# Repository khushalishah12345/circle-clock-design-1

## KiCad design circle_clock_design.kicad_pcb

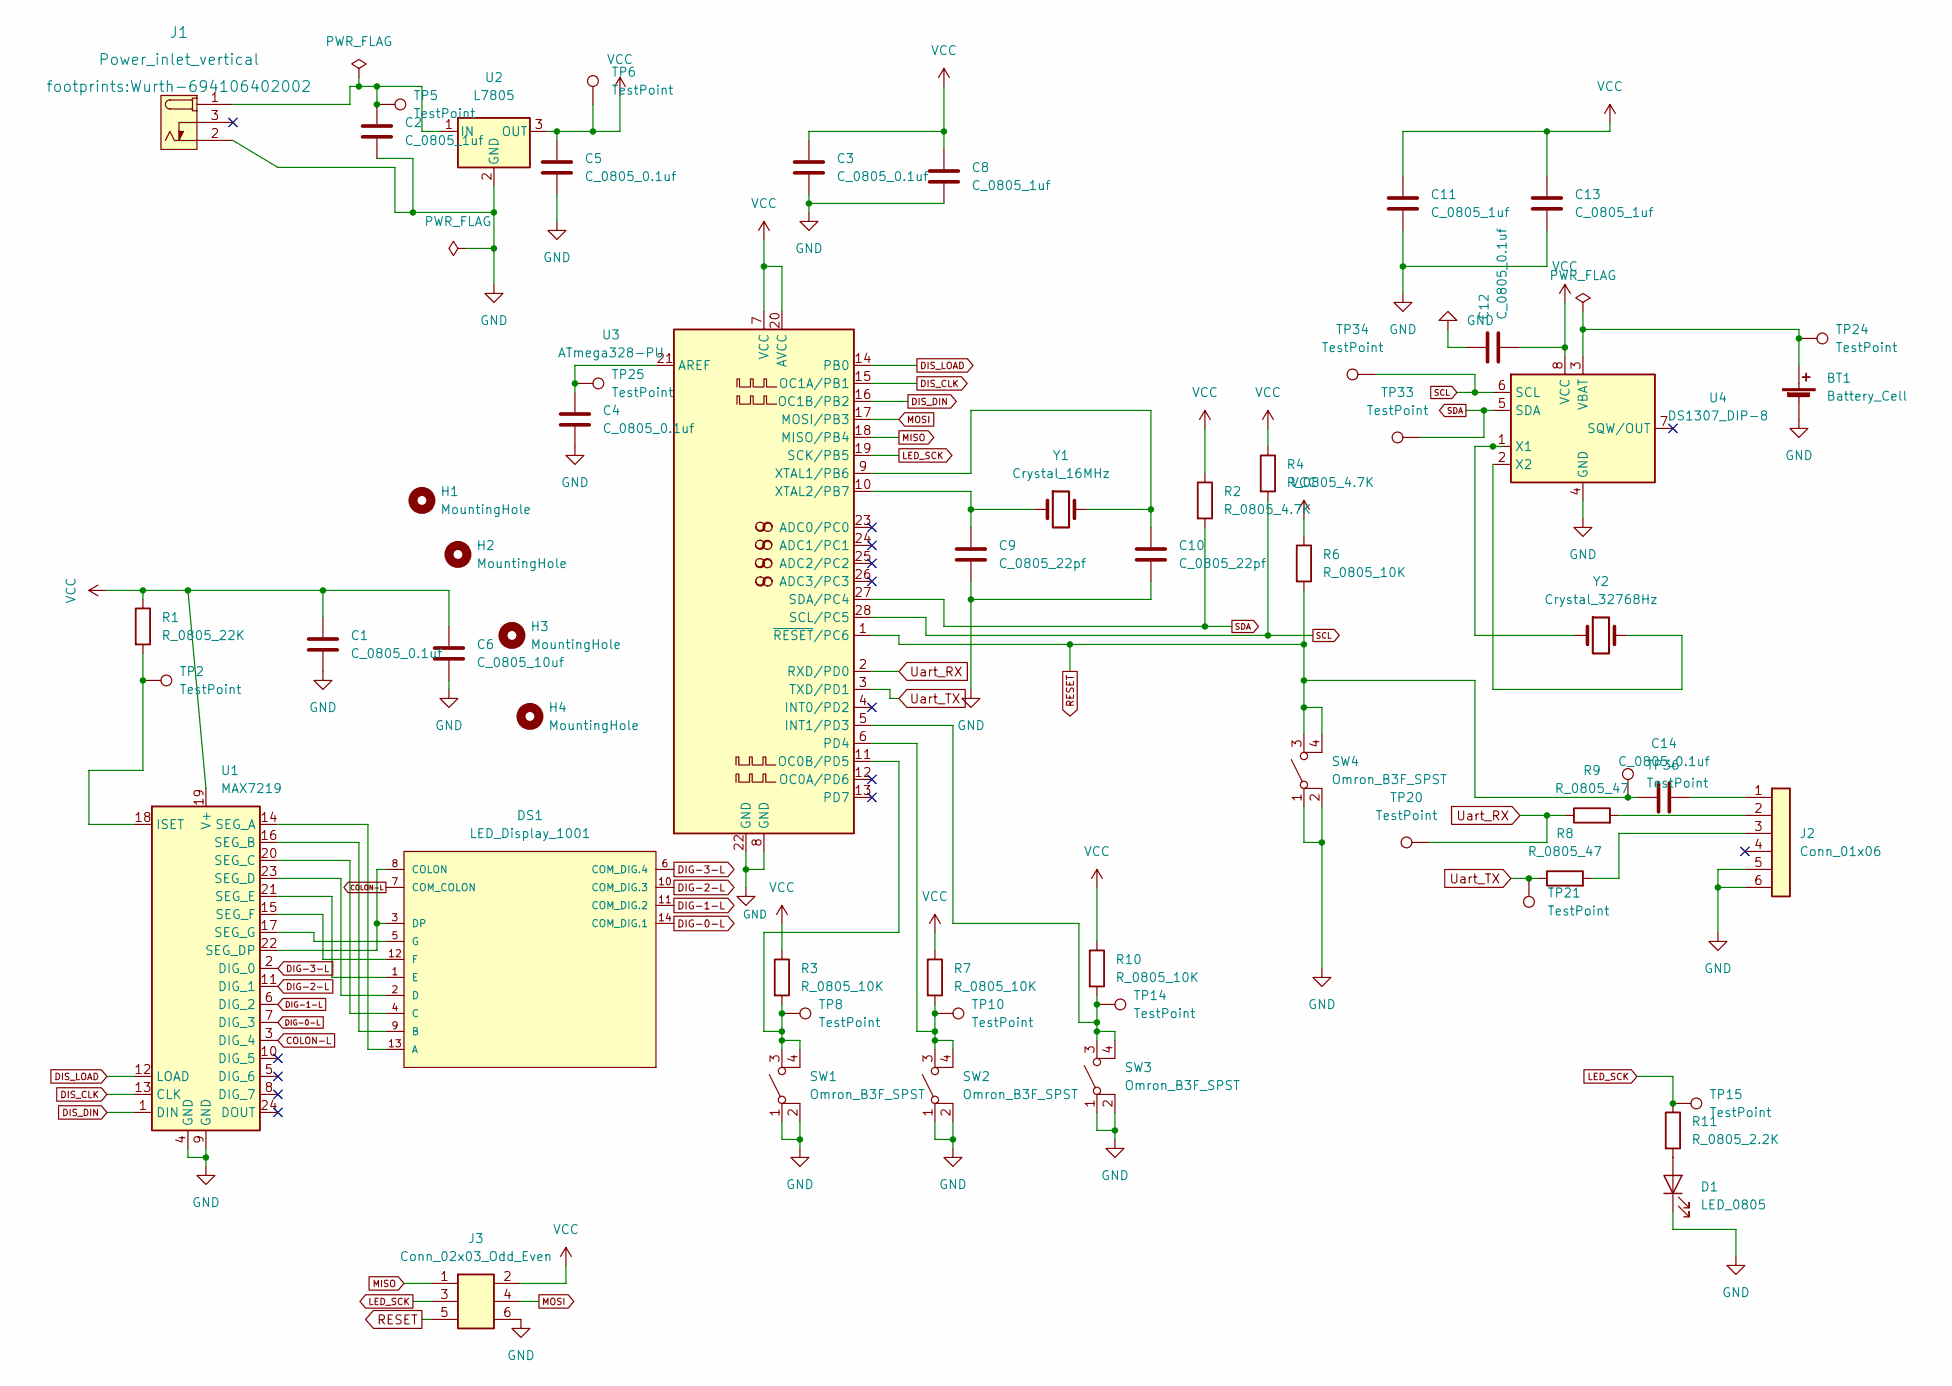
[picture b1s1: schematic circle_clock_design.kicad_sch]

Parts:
BT1: Battery_Cell; BatteryHolder_Keystone_106_1x20mm; MPN BS-7; Digikey PN BS-7-ND
C1, C3, C4, C5, C12, C14: C_0805_0.1uf; C_0805_2012Metric; Voltage N/A; Tolerance N/A; MPN 08055C104KAT2A; Digikey PN 478-1395-1-ND
C2, C8, C11, C13: C_0805_1uf; C_0805_2012Metric; Voltage N/A; Tolerance N/A; MPN CC0805KKX7R8BB105; Digikey PN 311-1456-1-ND
C6: C_0805_10uf; C_0805_2012Metric; Voltage N/A; Tolerance N/A; MPN GRM21BR61E106KA73L; Digikey PN 490-5523-1-ND
C9, C10: C_0805_22pf; C_0805_2012Metric; Voltage N/A; Tolerance N/A; MPN CC0805JRNPO9BN220; Digikey PN 311-1103-1-ND
D1: LED_0805; LED_0805_2012Metric; MPN 150080RS75000; Digikey PN 732-4984-1-ND
DS1: LED_Display_1001; Adafruit-1001-0-0-MFG; forward voltage 3.2V; reverse voltage 5V; mouser part number 485-1001; digikey description WHITE 7-SEGMENT CLOCK DISPLAY
H1, H2, H3, H4: MountingHole; MountingHole_3.2mm_M3
J1: Power_inlet_vertical; Wurth-694106402002; MPN 694106402002; Digikey PN 732-5931-ND
J2: Conn_01x06; PinHeader_1x06_P2.54mm_Vertical; MPN 61300611121; Digikey PN 732-5319-ND
J3: Conn_02x03_Odd_Even; PinHeader_2x03_P2.54mm_Vertical; MPN PRPC003DAAN-RC; Digikey PN S2011EC-03-ND
R1: R_0805_22K; R_0805_2012Metric; Tolerance N/A; MPN RC0805FR-0722KL; Digikey PN 311-22.0KCRCT-ND
R2, R4: R_0805_4.7K; R_0805_2012Metric; Tolerance N/A; MPN RC0805FR-074K7L; Digikey PN 311-4.70KCRCT-ND
R3, R6, R7, R10: R_0805_10K; R_0805_2012Metric; Tolerance N/A; MPN RC0805FR-0710KL; Digikey PN 311-10.0KCRCT-ND
R8, R9: R_0805_47; R_0805_2012Metric; Tolerance N/A; Mouser PN N/A; Digikey PN RC0805FR-0747RL
R11: R_0805_2.2K; R_0805_2012Metric; Tolerance N/A; MPN N/A; Digikey PN 311-2.20KCRCT-ND
SW1, SW2, SW3, SW4: Omron_B3F_SPST; SW_SPST_Omron_B3FS-100xP; MPN B3FS-1000P; Digikey PN SW423CT-ND
TP2, TP5, TP6, TP8, TP10, TP14, TP15, TP20, TP21, TP24, TP25, TP33, TP34, TP36: TestPoint; TestPoint_THTPad_D2.0mm_Drill1.0mm
U1: MAX7219; DIP-24_W7.62mm; MPN ED241DT; Digikey PN ED3049-5-ND
U2: L7805; TO-252-2; MPN L7805CDT-TR; Digikey PN 497-7255-1-ND
U3: ATmega328-PU; DIP-28_W7.62mm; MPN ED281DT; Digikey PN ED3050-5-ND
U4: DS1307_DIP-8; DIP-8_W7.62mm; MPN A 08-LC-TT; Digikey PN AE9986-ND
Y1: Crystal_16MHz; Crystal_SMD_HC49-SD; MPN ECS-160-20-5PXDN-TR; Digikey PN XC1299CT-ND
Y2: Crystal_32768Hz; Crystal_SMD_2Pin_3.2x1.5mm; MPN Q 0,032768-JTX310-12,5-20-T1-HMR-50K-LF; Digikey PN 1908-1314-1-ND

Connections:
COLON-L: DS1.7 (COM_COLON), U1.3 (DIG_4)
DIG-0-L: DS1.14 (COM_DIG.1), U1.7 (DIG_3)
DIG-1-L: DS1.11 (COM_DIG.2), U1.6 (DIG_2)
DIG-2-L: DS1.10 (COM_DIG.3), U1.11 (DIG_1)
DIG-3-L: DS1.6 (COM_DIG.4), U1.2 (DIG_0)
DIS_CLK: U1.13 (CLK), U3.15 (OC1A/PB1)
DIS_DIN: U1.1 (DIN), U3.16 (OC1B/PB2)
DIS_LOAD: U1.12 (LOAD), U3.14 (PB0)
GND: BT1.2 (-), C1.2, C2.2, C3.2, C4.2, C5.2, C6.2, C8.2, C9.2, C10.2, C11.2, C12.1, C13.2, D1.1 (K), J1.2 (OUT), J2.5, J2.6, J3.6, SW1.1 (A), SW1.2 (A), SW2.1 (A), SW2.2 (A), SW3.1 (A), SW3.2 (A), SW4.1 (A), SW4.2 (A), U1.4 (GND), U1.9 (GND), U2.2 (GND), U3.8 (GND), U3.22 (GND), U4.4 (GND)
LED_SCK: J3.3, R11.1, TP15.1, U3.19 (SCK/PB5)
MISO: J3.1, U3.18 (MISO/PB4)
MOSI: J3.4, U3.17 (MOSI/PB3)
unnamed: BT1.1 (+), TP24.1, U4.3 (VBAT)
unnamed: C4.1, TP25.1, U3.21 (AREF)
unnamed: C9.1, U3.10 (XTAL2/PB7), Y1.1
unnamed: C10.1, U3.9 (XTAL1/PB6), Y1.2
unnamed: C14.2, J2.1
unnamed: D1.2 (A), R11.2
unnamed: DS1.1 (E), U1.21 (SEG_E)
unnamed: DS1.2 (D), U1.23 (SEG_D)
unnamed: DS1.3 (DP), DS1.8 (COLON), U1.22 (SEG_DP)
unnamed: DS1.4 (C), U1.20 (SEG_C)
unnamed: DS1.5 (G), U1.17 (SEG_G)
unnamed: DS1.9 (B), U1.16 (SEG_B)
unnamed: DS1.12 (F), U1.15 (SEG_F)
unnamed: DS1.13 (A), U1.14 (SEG_A)
unnamed: C2.1, J1.1 (POLE), TP5.1, U2.1 (IN)
unnamed: J2.2, R9.2
unnamed: J2.3, R8.2
unnamed: R1.2, TP2.1, U1.18 (ISET)
unnamed: R3.2, SW1.3 (B), SW1.4 (B), TP8.1, U3.11 (OC0B/PD5)
unnamed: R7.2, SW2.3 (B), SW2.4 (B), TP10.1, U3.6 (PD4)
unnamed: R10.2, SW3.3 (B), SW3.4 (B), TP14.1, U3.5 (INT1/PD3)
unnamed: U4.1 (X1), Y2.1
unnamed: U4.2 (X2), Y2.2
RESET: C14.1, J3.5, R6.2, SW4.3 (B), SW4.4 (B), TP36.1, U3.1 (~RESET/PC6)
SCL: R4.2, TP34.1, U3.28 (SCL/PC5), U4.6 (SCL)
SDA: R2.2, TP33.1, U3.27 (SDA/PC4), U4.5 (SDA)
Uart_RX: R9.1, TP20.1, U3.2 (RXD/PD0)
Uart_TX: R8.1, TP21.1, U3.3 (TXD/PD1)
VCC: C1.1, C3.1, C5.1, C6.1, C8.1, C11.1, C12.2, C13.1, J3.2, R1.1, R2.1, R3.1, R4.1, R6.1, R7.1, R10.1, TP6.1, U1.19 (V+), U2.3 (OUT), U3.7 (VCC), U3.20 (AVCC), U4.8 (VCC)

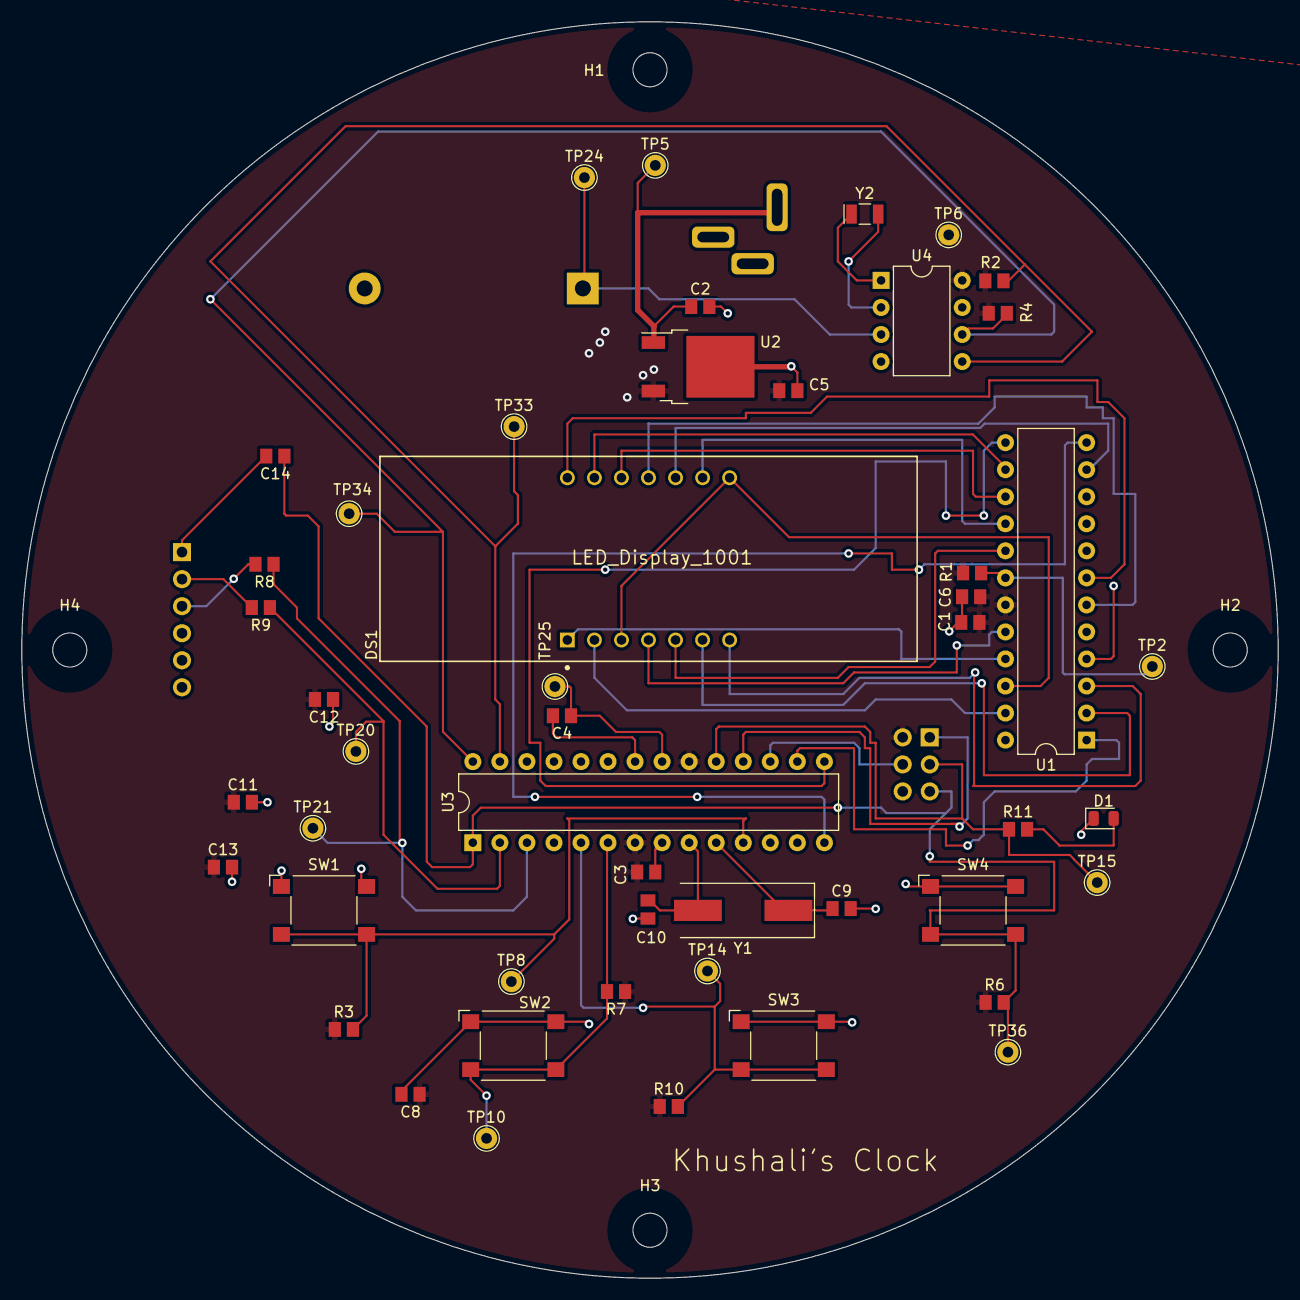
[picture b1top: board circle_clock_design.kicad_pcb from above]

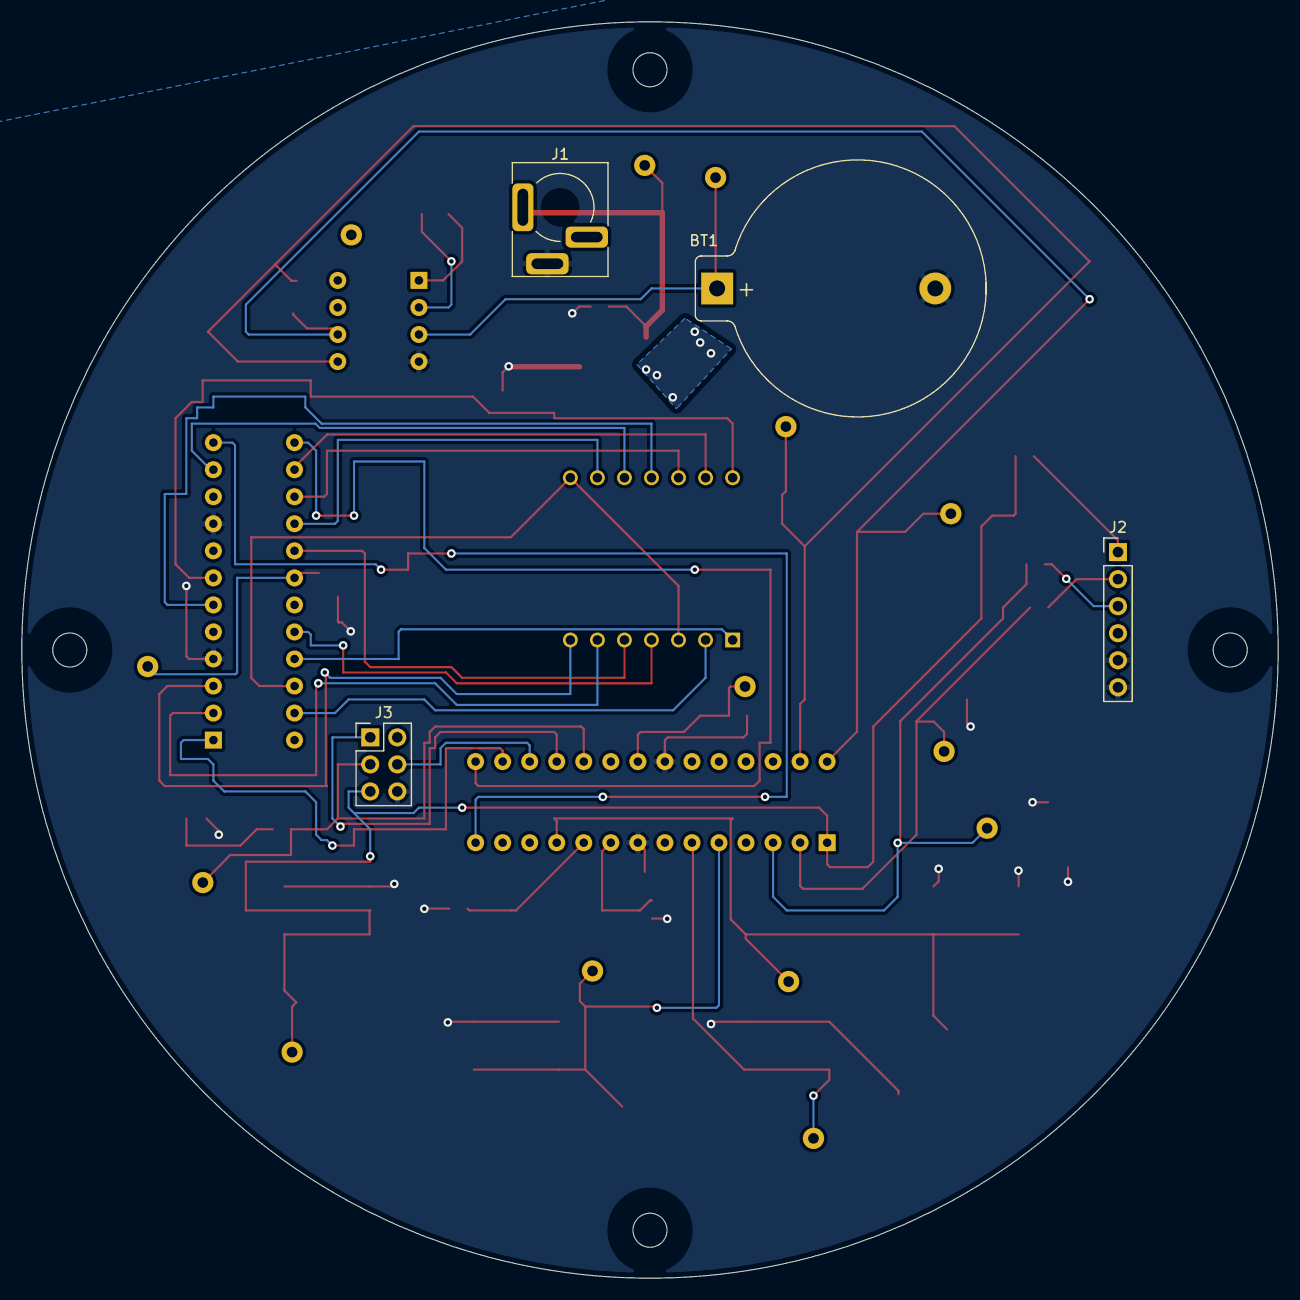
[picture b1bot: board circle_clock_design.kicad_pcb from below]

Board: 2 copper layers, 118.0 x 118.0 mm, 57 parts (4 on the bottom side), 41 nets.
